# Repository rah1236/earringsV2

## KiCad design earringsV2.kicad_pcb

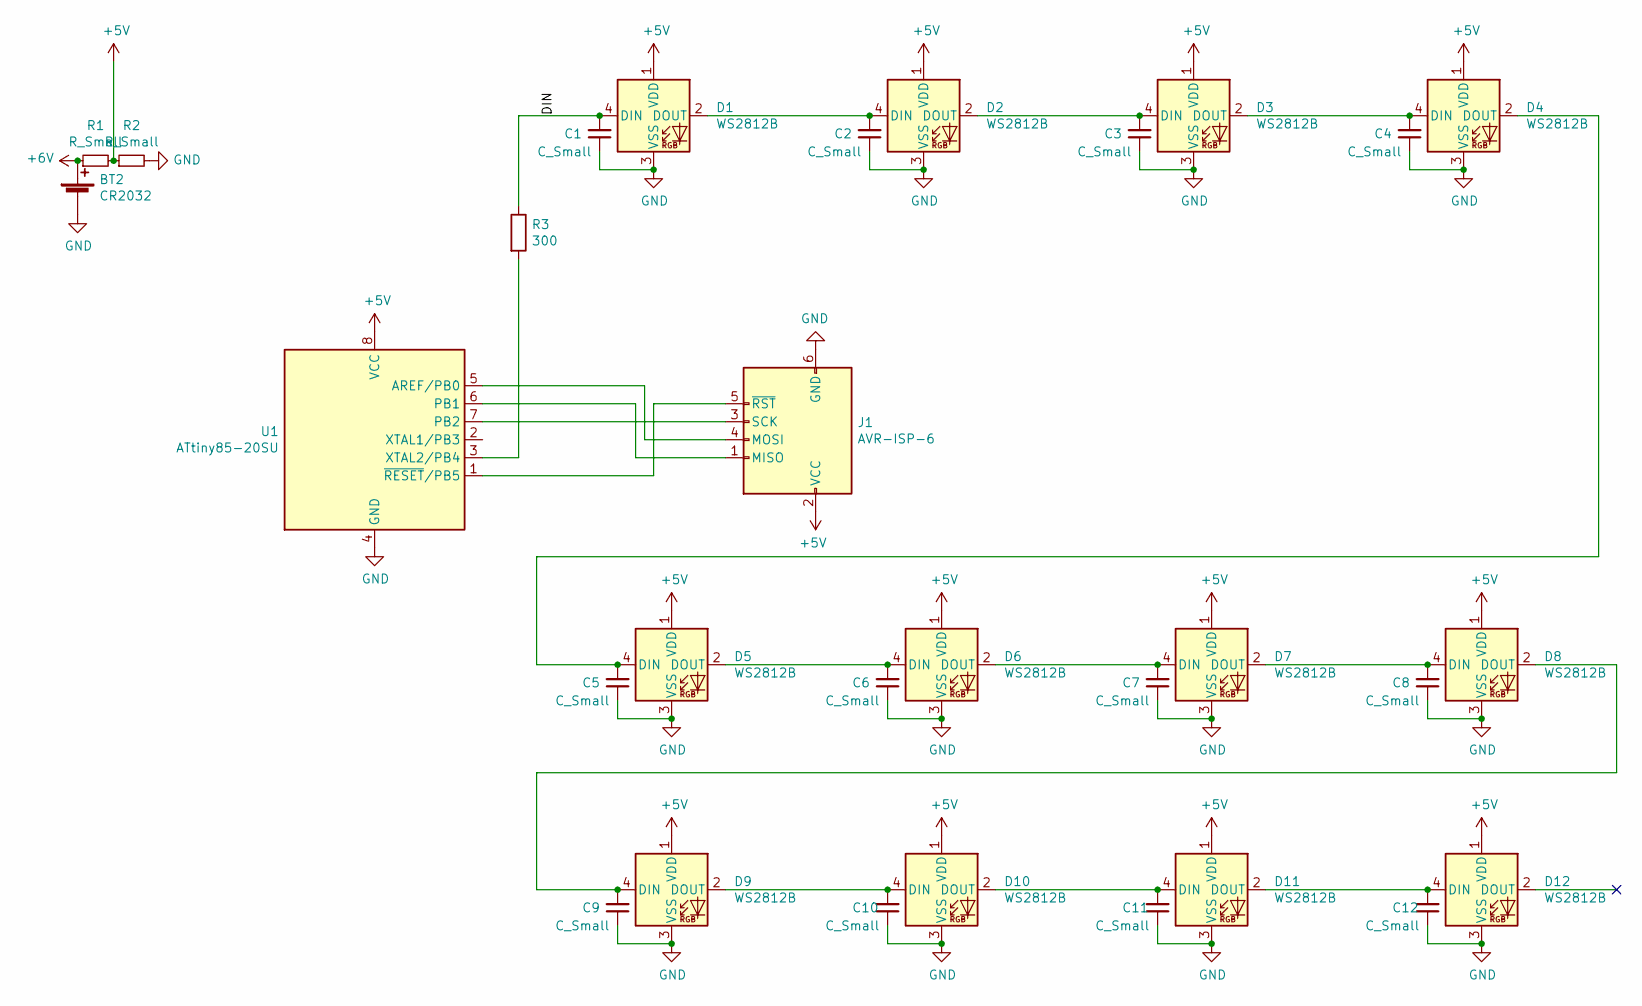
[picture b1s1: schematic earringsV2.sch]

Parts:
BT2: CR2032; 3025-2
C1, C2, C3, C4, C5, C6, C7, C8, C9, C10, C11, C12: C_Small; C_0805_2012Metric_Pad1.18x1.45mm_HandSolder
D1, D2, D3, D4, D5, D6, D7, D8, D9, D10, D11, D12: WS2812B; LED_WS2812B_PLCC4_5.0x5.0mm_P3.2mm
J1: AVR-ISP-6; PinSocket_2x03_P2.54mm_Vertical_SMD
R1, R2: R_Small; C_0805_2012Metric_Pad1.18x1.45mm_HandSolder
R3: 300; R_0603_1608Metric_Pad0.98x0.95mm_HandSolder
U1: ATtiny85-20SU; SOIJ-8_5.3x5.3mm_P1.27mm

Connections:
+5V: D1.1 (VDD), D2.1 (VDD), D3.1 (VDD), D4.1 (VDD), D5.1 (VDD), D6.1 (VDD), D7.1 (VDD), D8.1 (VDD), D9.1 (VDD), D10.1 (VDD), D11.1 (VDD), D12.1 (VDD), J1.2 (VCC), R1.2, R2.1, U1.8 (VCC)
+6V: BT2.1 (+), R1.1
/DIN: C1.2, D1.4 (DIN), R3.1
GND: BT2.2 (-), C1.1, C2.1, C3.1, C4.1, C5.1, C6.1, C7.1, C8.1, C9.1, C10.1, C11.1, C12.1, D1.3 (VSS), D2.3 (VSS), D3.3 (VSS), D4.3 (VSS), D5.3 (VSS), D6.3 (VSS), D7.3 (VSS), D8.3 (VSS), D9.3 (VSS), D10.3 (VSS), D11.3 (VSS), D12.3 (VSS), J1.6 (GND), R2.2, U1.4 (GND)
unnamed: C2.2, D1.2 (DOUT), D2.4 (DIN)
unnamed: C3.2, D2.2 (DOUT), D3.4 (DIN)
unnamed: C4.2, D3.2 (DOUT), D4.4 (DIN)
unnamed: C5.2, D4.2 (DOUT), D5.4 (DIN)
unnamed: C6.2, D5.2 (DOUT), D6.4 (DIN)
unnamed: C7.2, D6.2 (DOUT), D7.4 (DIN)
unnamed: C8.2, D7.2 (DOUT), D8.4 (DIN)
unnamed: C9.2, D8.2 (DOUT), D9.4 (DIN)
unnamed: C10.2, D9.2 (DOUT), D10.4 (DIN)
unnamed: C11.2, D10.2 (DOUT), D11.4 (DIN)
unnamed: C12.2, D11.2 (DOUT), D12.4 (DIN)
unnamed: J1.1 (MISO), U1.6 (PB1)
unnamed: J1.3 (SCK), U1.7 (PB2)
unnamed: J1.4 (MOSI), U1.5 (AREF/PB0)
unnamed: J1.5 (~RST), U1.1 (~RESET~/PB5)
unnamed: R3.2, U1.3 (XTAL2/PB4)

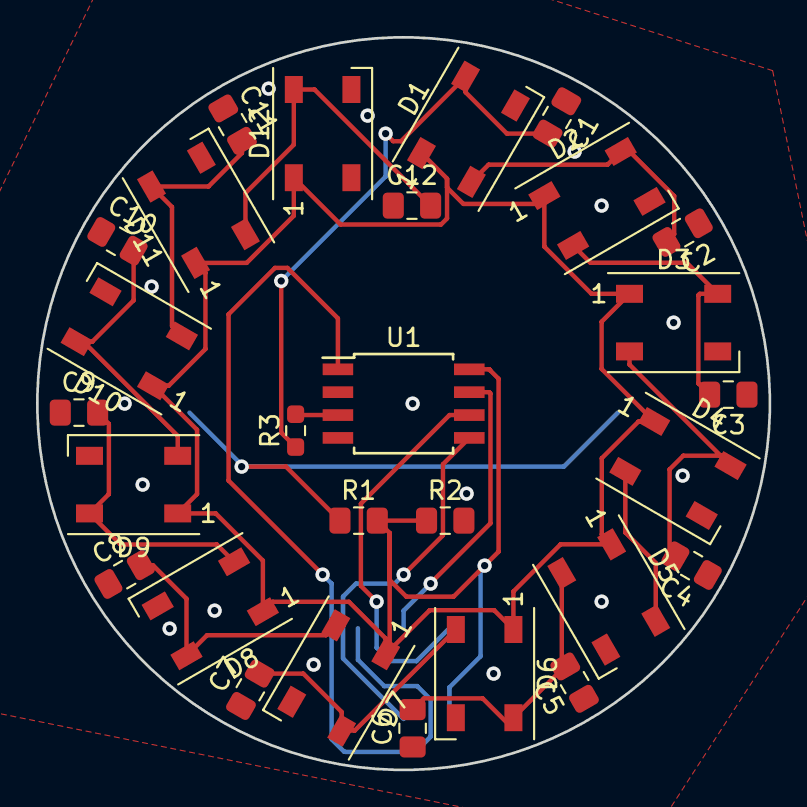
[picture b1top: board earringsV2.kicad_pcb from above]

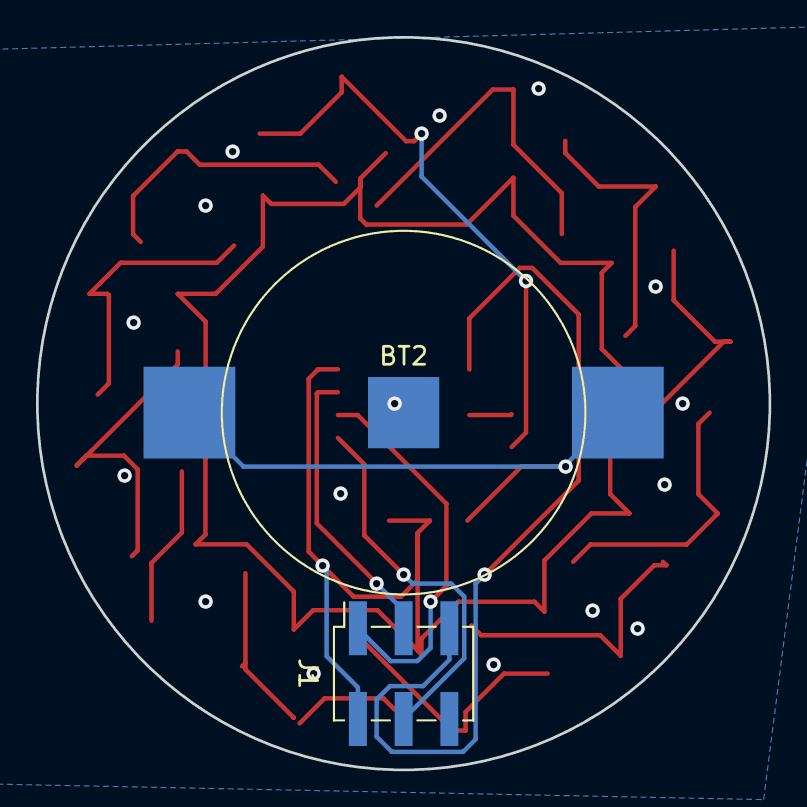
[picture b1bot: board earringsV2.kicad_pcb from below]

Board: 2 copper layers, 40.7 x 40.7 mm, 30 parts (2 on the bottom side), 20 nets.

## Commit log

2022-01-27 init
